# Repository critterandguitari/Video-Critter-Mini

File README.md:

Video-Critter-Mini
==================

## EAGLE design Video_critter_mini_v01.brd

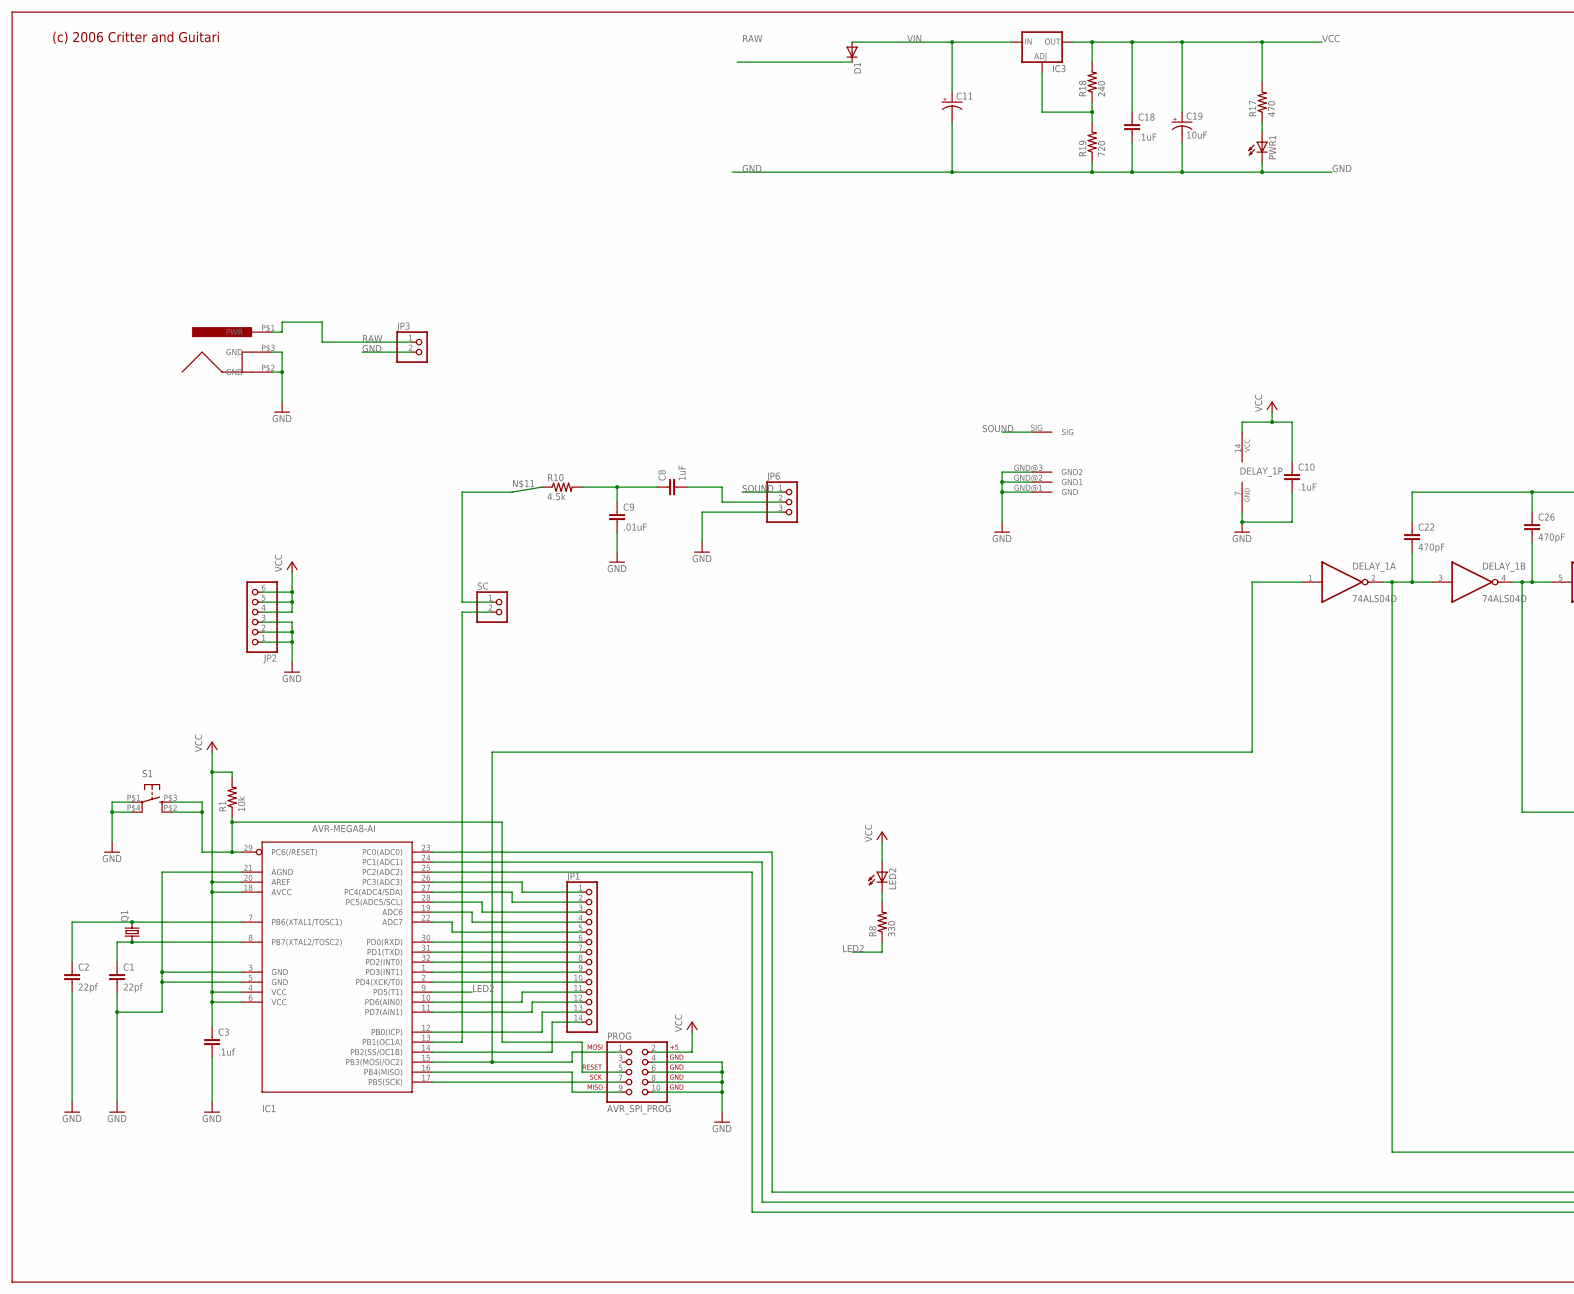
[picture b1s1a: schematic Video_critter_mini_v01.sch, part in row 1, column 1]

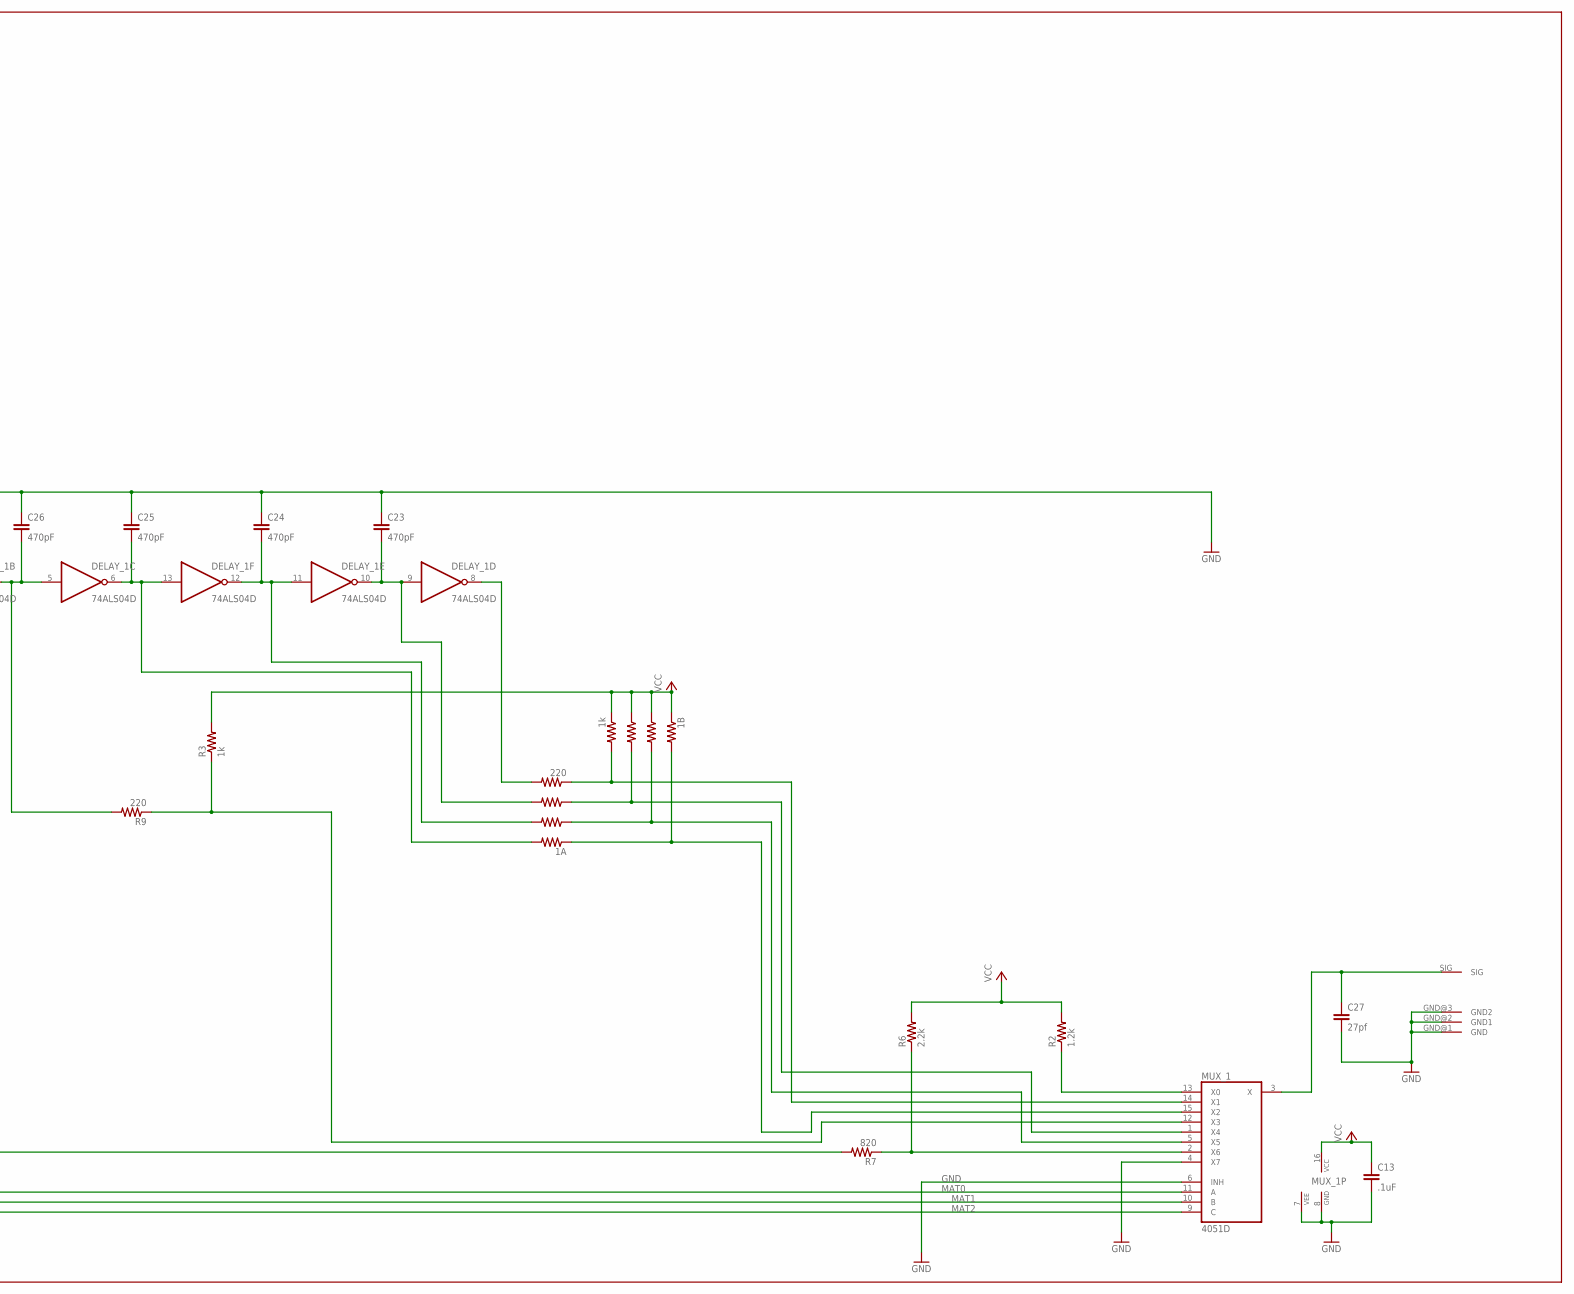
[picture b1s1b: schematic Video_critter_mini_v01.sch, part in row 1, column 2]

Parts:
1A: 220; 1206X4RESISTOR
1B: 1k; 1206X4RESISTOR
C1, C2: 22pf; C0603
C3: .1uf; C0603
C8: 1uF; C0603
C9: .01uF; C0603
C10, C13, C18: .1uF; C0603
C11: CPOL-USE3.5-8; E3,5-8
C19: 10uF; CPOL_1206
C22, C23, C24, C25, C26: 470pF; C0603
C27: 27pf; C0603
D1: DIODESMB; SMB
DELAY_1: 74ALS04D; SO14
IC1: AVR-MEGA8-AI; TQFP32-08
IC3: V_REG_FAN1117SOT223; SOT223
JP1: PINHD-1X14; 1X14
JP2: PINHD-1X6; 1X06
JP3: PINHD-1X2; 1X02
JP6: PINHD-1X3; 1X03
LED2: LED1206; CHIPLED_1206
MUX_1: 4051D; SO16
PROG: AVR_SPI_PROG; PINHEAD_2X05
PWR1: LED1206; CHIPLED_1206
Q1: CRYSTALHC49UV; HC49U-V
R1: 10k; R0603
R2: 1.2k; R0603
R3: 1k; R0603
R6: 2.2k; R0603
R7: 820; R0603
R8: 330; R0603
R9: 220; R0603
R10: 4.5k; R0603
R17: 470; R0603
R18: 240; R0603
R19: 720; R0603
S1: TAC_SWITCH; TACTILE_SWITCH_SMD
SC: PINHD-1X2; 1X02
U$1: POWER_JACK
U$5, U$6: PHONO_PLUG; PHONO_PCB

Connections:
BURST: C22.2, DELAY_1.2 (O), DELAY_1.3 (I), R7.2
COLORS: DELAY_1.1 (I), IC1.15 (PB3(MOSI/OC2)), PROG.1
GND: C1.2, C2.2, C3.2, C9.2, C10.2, C11.-, C13.2, C18.2, C19.C (-), C22.1, C23.1, C24.1, C25.1, C26.1, C27.2, DELAY_1.7 (GND), IC1.3 (GND), IC1.5 (GND), IC1.21 (AGND), JP2.1, JP2.2, JP2.3, JP3.2, JP6.3, MUX_1.4 (X7), MUX_1.6 (INH), MUX_1.7 (VEE), MUX_1.8 (GND), PROG.4, PROG.6, PROG.8, PROG.10, PWR1.C, R19.1, S1.P$1, S1.P$4 (P1), U$1.P$2 (GND), U$1.P$3 (GND), U$5.GND@1 (GND), U$5.GND@2 (GND1), U$5.GND@3 (GND2), U$6.GND@1 (GND), U$6.GND@2 (GND1), U$6.GND@3 (GND2)
LED2: IC1.9 (PD5(T1)), R8.1
MAT0: IC1.23 (PC0(ADC0)), MUX_1.11 (A)
MAT1: IC1.24 (PC1(ADC1)), MUX_1.10 (B)
MAT2: IC1.25 (PC2(ADC2)), MUX_1.9 (C)
unnamed: IC1.13 (PB1(OC1A)), SC.2
unnamed: 1A.P$2 (5), DELAY_1.8 (O)
unnamed: 1A.P$4 (2), C23.2, DELAY_1.9 (I), DELAY_1.10 (O)
unnamed: C2.1, IC1.7 (PB6(XTAL1/TOSC1)), Q1.2
unnamed: C1.1, IC1.8 (PB7(XTAL2/TOSC2)), Q1.1
unnamed: C8.1, C9.1, R10.2
unnamed: C26.2, DELAY_1.4 (O), DELAY_1.5 (I), R9.2
unnamed: MUX_1.12 (X3), R3.1, R9.1
unnamed: C8.2, JP6.2
unnamed: IC1.29 (PC6(/RESET)), PROG.5, R1.1, S1.P$2 (S1), S1.P$3 (S)
unnamed: R10.1, SC.1
unnamed: IC1.26 (PC3(ADC3)), JP1.1
unnamed: IC3.1 (ADJ), R18.1, R19.2
unnamed: IC1.27 (PC4(ADC4/SDA)), JP1.2
unnamed: IC1.28 (PC5(ADC5/SCL)), JP1.3
unnamed: IC1.17 (PB5(SCK)), PROG.7
unnamed: IC1.16 (PB4(MISO)), PROG.9
unnamed: IC1.19 (ADC6), JP1.4
unnamed: IC1.22 (ADC7), JP1.5
unnamed: IC1.30 (PD0(RXD)), JP1.6
unnamed: LED2.C, R8.2
unnamed: IC1.31 (PD1(TXD)), JP1.7
unnamed: IC1.32 (PD2(INT0)), JP1.8
unnamed: PWR1.A, R17.1
unnamed: IC1.1 (PD3(INT1)), JP1.9
unnamed: IC1.2 (PD4(XCK/T0)), JP1.10
unnamed: IC1.10 (PD6(AIN0)), JP1.11
unnamed: IC1.11 (PD7(AIN1)), JP1.12
unnamed: IC1.12 (PB0(ICP)), JP1.13
unnamed: IC1.14 (PB2(SS/OC1B)), JP1.14
unnamed: 1A.P$8 (7), C25.2, DELAY_1.6 (O), DELAY_1.13 (I)
unnamed: 1A.P$6 (3), C24.2, DELAY_1.11 (I), DELAY_1.12 (O)
unnamed: MUX_1.13 (X0), R2.1
unnamed: 1A.P$1 (6), 1B.P$2 (5), MUX_1.14 (X1)
unnamed: 1A.P$3 (1), 1B.P$4 (2), MUX_1.1 (X4)
unnamed: 1A.P$5 (4), 1B.P$6 (3), MUX_1.5 (X5)
unnamed: 1A.P$7 (8), 1B.P$8 (7), MUX_1.15 (X2)
unnamed: C27.1, MUX_1.3 (X), U$6.SIG
unnamed: MUX_1.2 (X6), R6.1, R7.1
RAW: D1.1 (C), JP3.1, U$1.P$1 (PWR)
SOUND: JP6.1, U$5.SIG
VCC: 1B.P$1 (6), 1B.P$3 (1), 1B.P$5 (4), 1B.P$7 (8), C3.1, C10.1, C13.1, C18.1, C19.A (+), DELAY_1.14 (VCC), IC1.4 (VCC), IC1.6 (VCC), IC1.18 (AVCC), IC1.20 (AREF), IC3.2 (OUT), JP2.4, JP2.5, JP2.6, LED2.A, MUX_1.16 (VCC), PROG.2, R1.2, R2.2, R3.2, R6.2, R17.2, R18.2
VIN: C11.+, D1.2 (A), IC3.3 (IN)

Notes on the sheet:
(c) 2006 Critter and Guitari

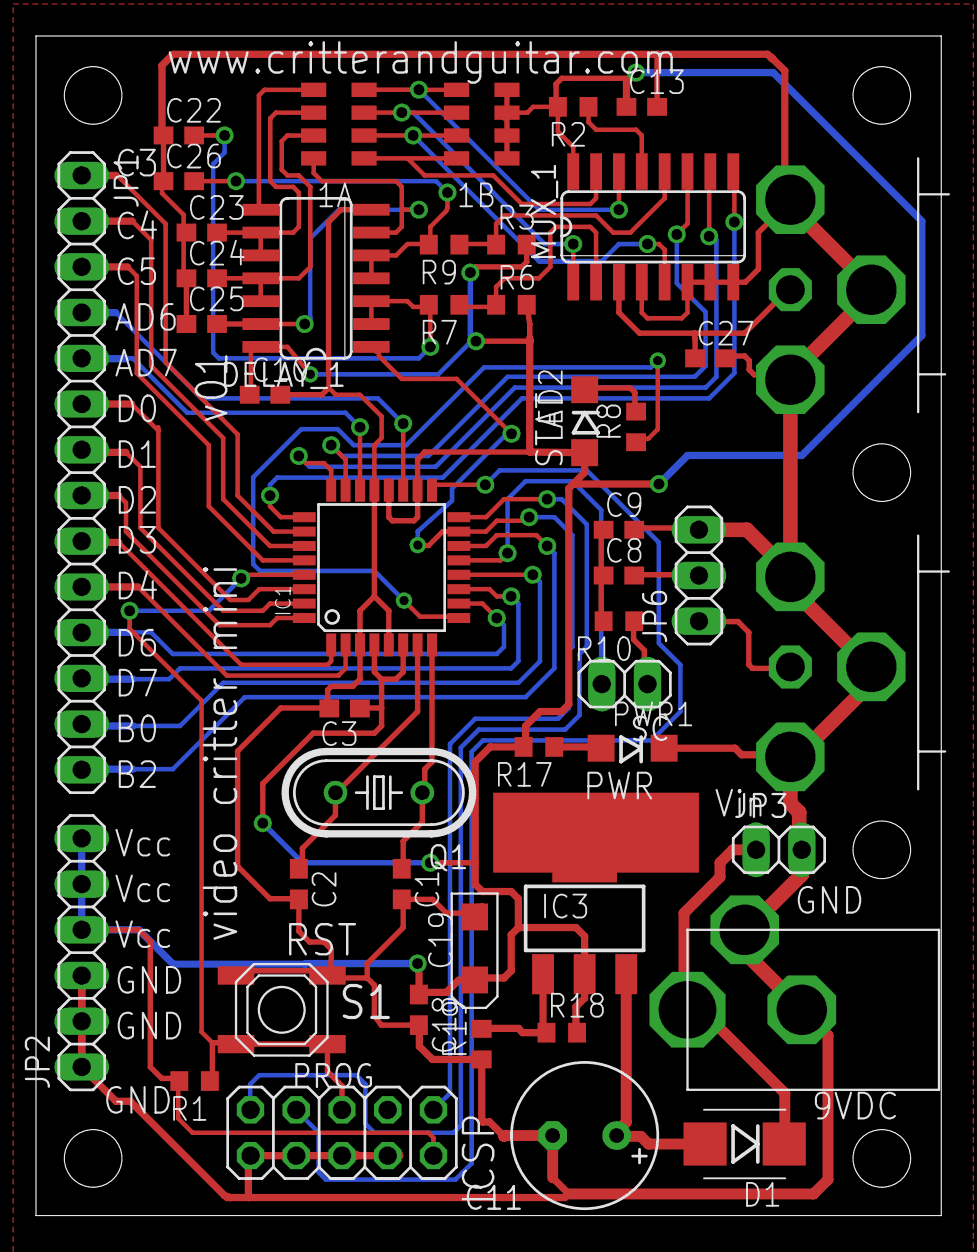
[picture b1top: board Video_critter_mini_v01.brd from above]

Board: 2 copper layers, 50.3 x 65.5 mm, 47 parts (0 on the bottom side), 50 nets.

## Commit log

2013-04-22 adding eagle files
